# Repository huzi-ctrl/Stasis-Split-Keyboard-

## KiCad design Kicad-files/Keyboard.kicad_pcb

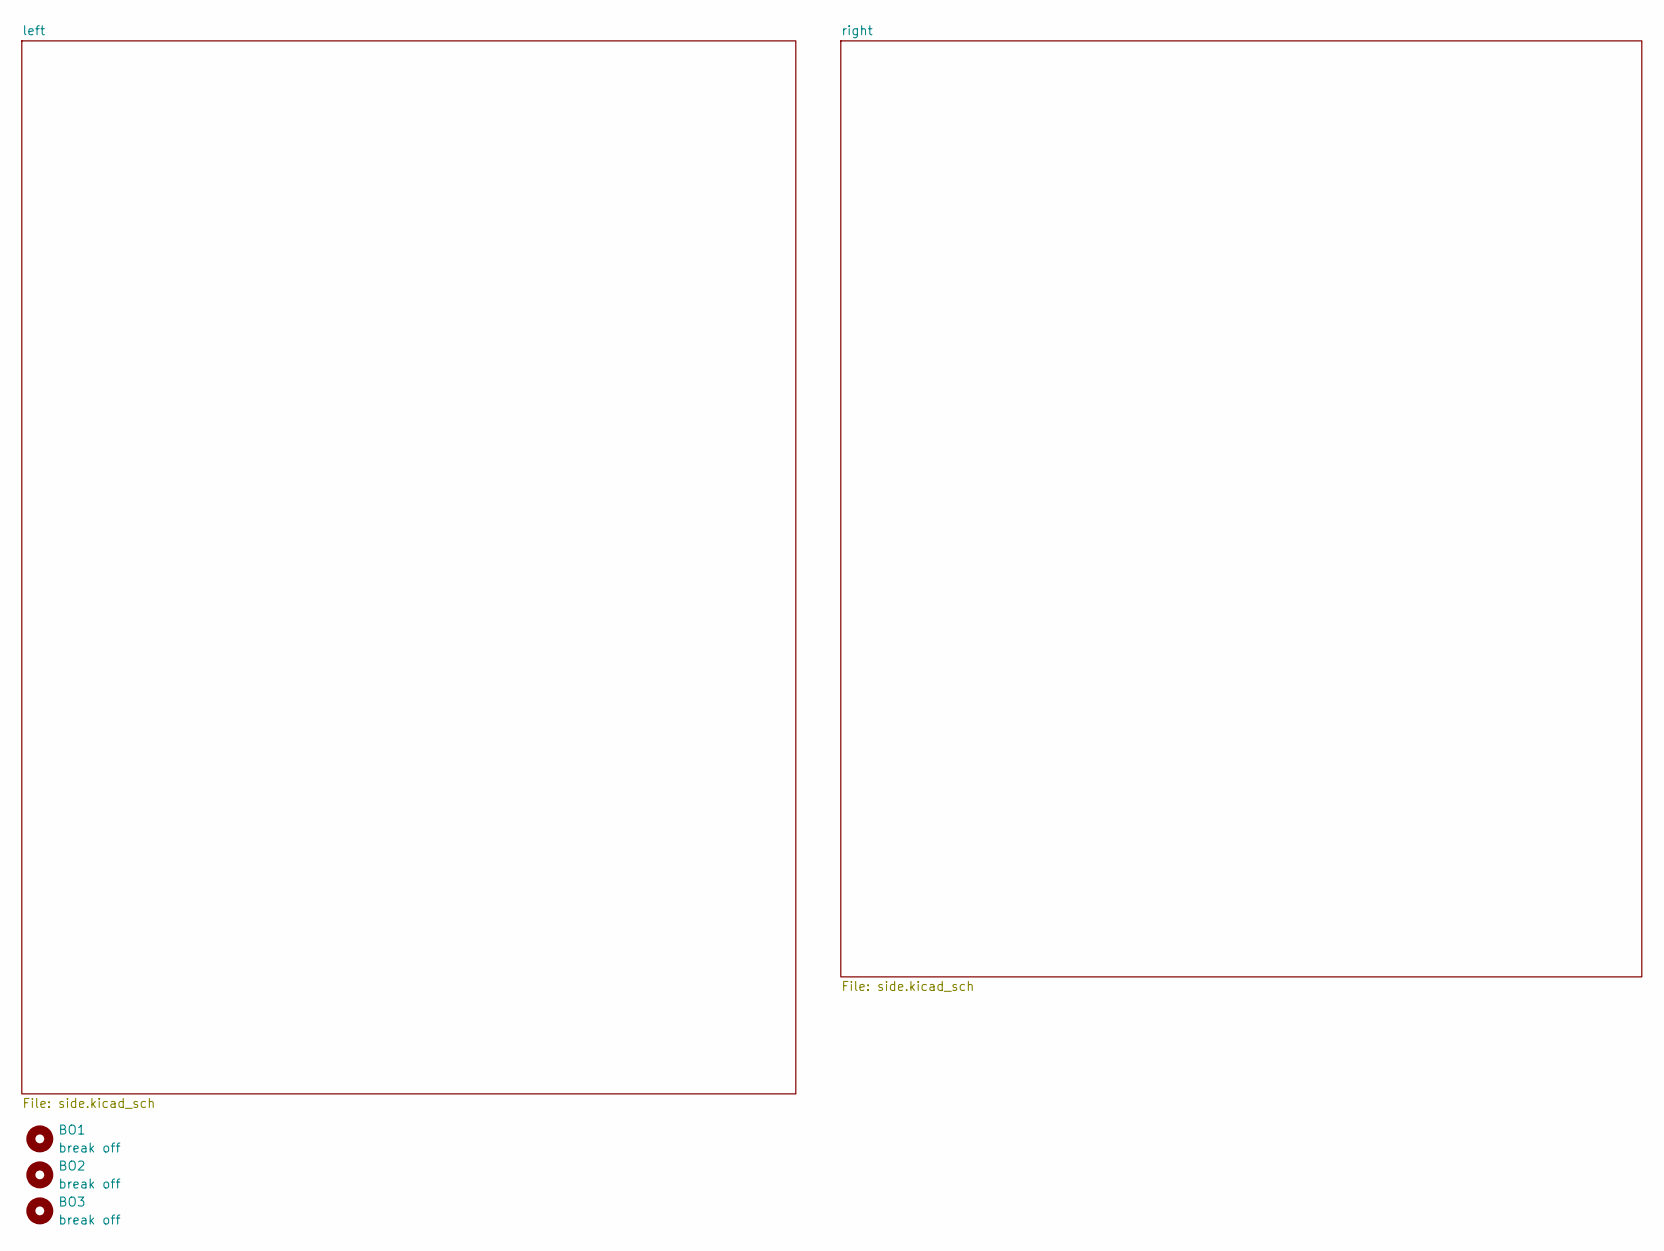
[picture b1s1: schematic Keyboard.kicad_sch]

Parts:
BO1, BO2, BO3: break off; MouseBite-Slot_2.0x4.5mm_outset_D0.5mm_P0.85mm_7h

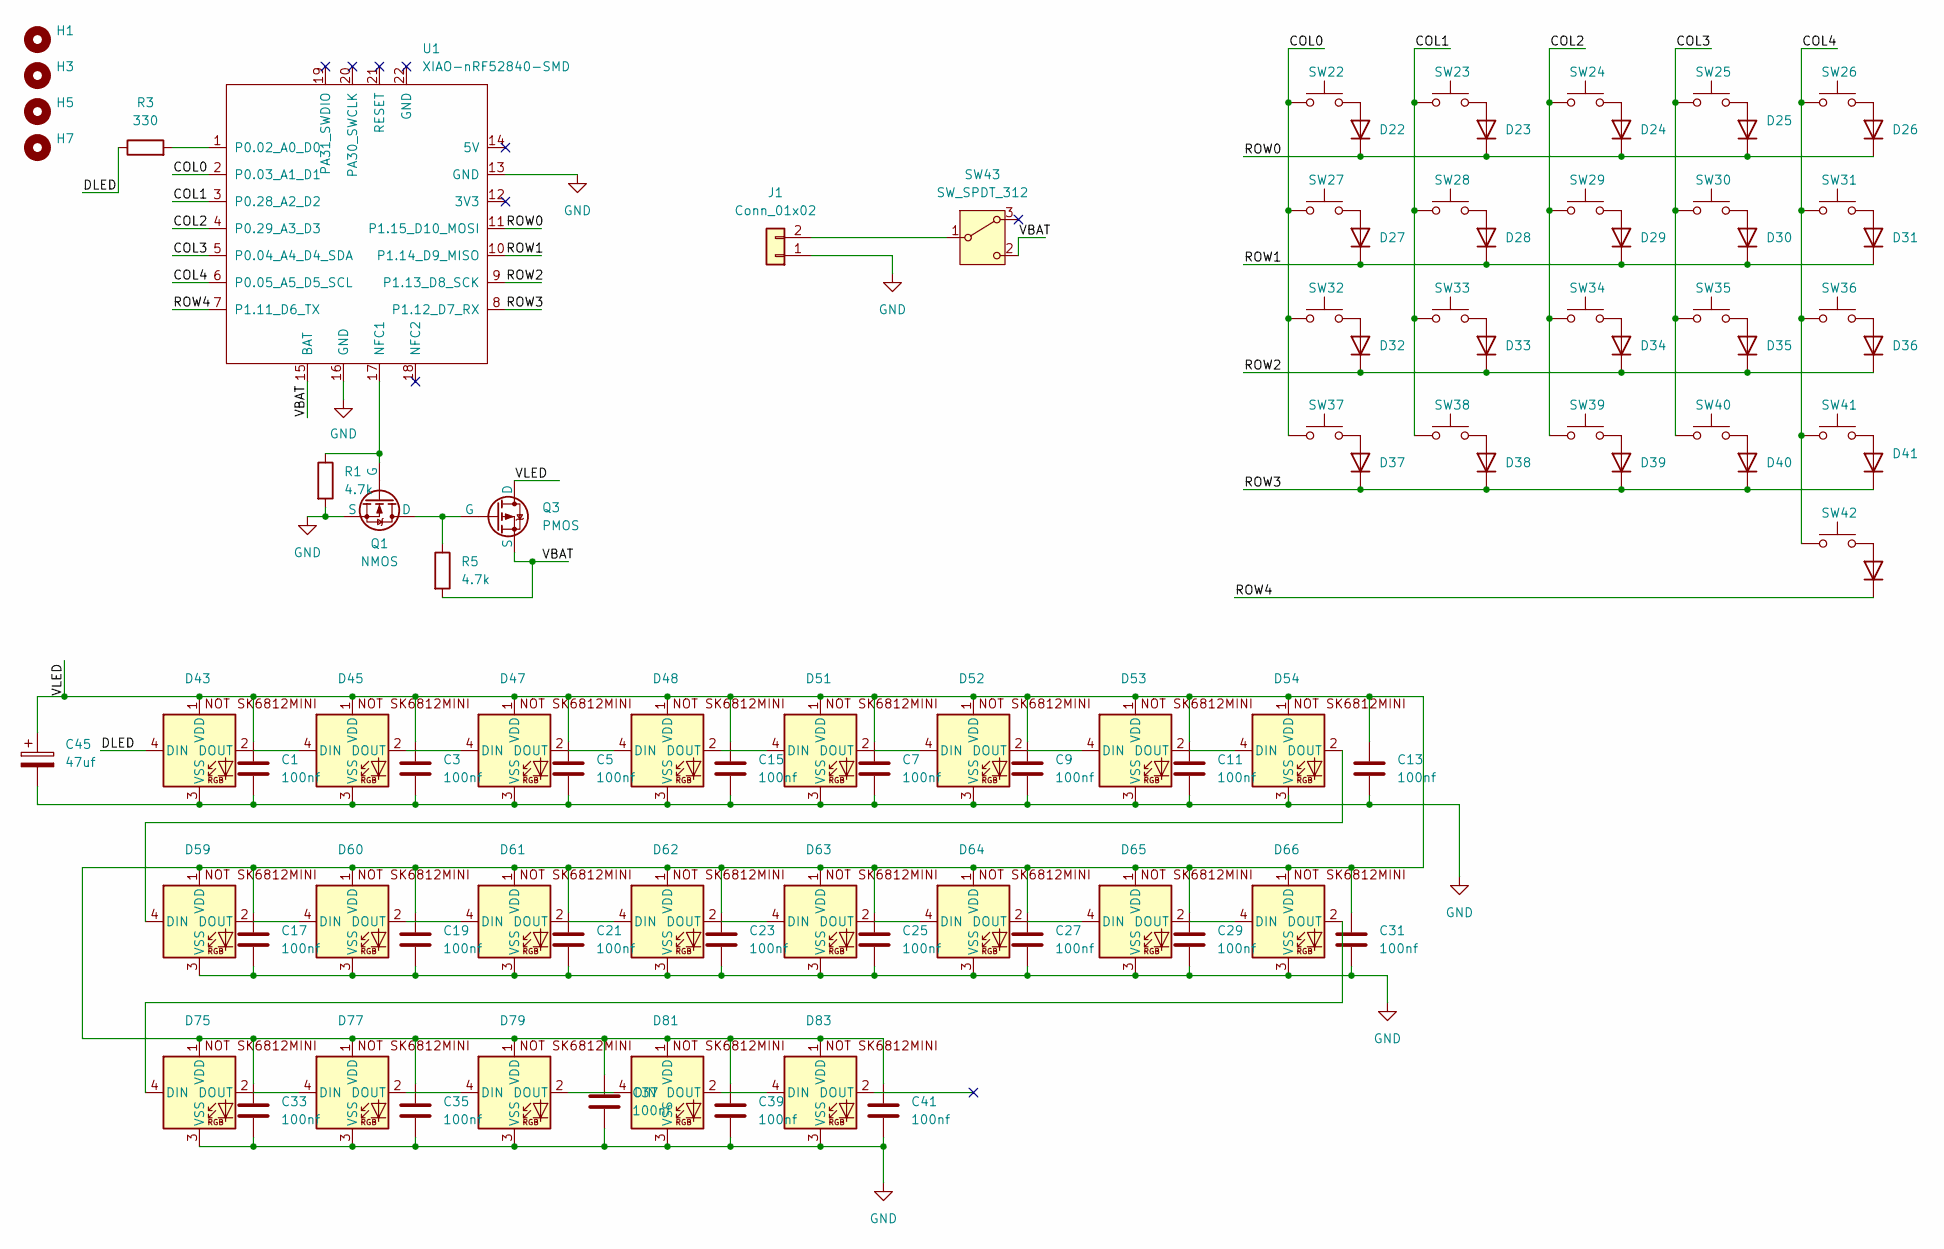
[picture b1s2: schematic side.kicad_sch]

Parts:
C1, C3, C5, C7, C9, C11, C13, C15, C17, C19, C21, C23, C25, C27, C29, C31, C33, C35, C37, C39, C41: 100nf; C_Disc_D5.0mm_W2.5mm_P5.00mm
C45: 47uf; CP_Radial_D8.0mm_P3.50mm
D22, D23, D24, D25, D26, D27, D28, D29, D30, D31, D32, D33, D34, D35, D36, D37, D38, D39, D40, D41, D42: D
D43, D45, D47, D48, D51, D52, D53, D54, D59, D60, D61, D62, D63, D64, D65, D66, D75, D77, D79, D81, D83: SK6812MINI-E; SK6812MINI-E - 3.2x2.8x1.78mm
H1, H3, H5, H7: MountingHole; MountingHole_2.2mm_M2
J1: Conn_01x02; JST_PH_S2B-PH-K_1x02_P2.00mm_Horizontal
Q1: NMOS; TO-92-2_Wide
Q3: PMOS; TO-220-3_Vertical
R1, R5: 4.7k; R_Axial_DIN0207_L6.3mm_D2.5mm_P10.16mm_Horizontal
R3: 330; R_Axial_DIN0207_L6.3mm_D2.5mm_P10.16mm_Horizontal
SW22, SW23, SW24, SW25, SW26, SW27, SW28, SW29, SW30, SW31, SW32, SW33, SW34, SW35, SW36, SW37, SW38, SW39, SW40, SW41, SW42: SW_Push
SW43: SW_SPDT_312; PinHeader_1x03_P2.54mm_Vertical
U1: XIAO-nRF52840-SMD; modified-XIAO-nRF52840-SMD

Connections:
/left/COL0: SW22.1, SW27.1, SW32.1, SW37.1, U1.2 (P0.03_A1_D1)
/left/COL1: SW23.1, SW28.1, SW33.1, SW38.1, U1.3 (P0.28_A2_D2)
/left/COL2: SW24.1, SW29.1, SW34.1, SW39.1, U1.4 (P0.29_A3_D3)
/left/COL3: SW25.1, SW30.1, SW35.1, SW40.1, U1.5 (P0.04_A4_D4_SDA)
/left/COL4: SW26.1, SW31.1, SW36.1, SW41.1, SW42.1, U1.6 (P0.05_A5_D5_SCL)
/left/DLED: D43.4 (DIN), R3.1
/left/ROW0: D22.1 (K), D23.1 (K), D24.1 (K), D25.1 (K), D26.1 (K), U1.11 (P1.15_D10_MOSI)
/left/ROW1: D27.1 (K), D28.1 (K), D29.1 (K), D30.1 (K), D31.1 (K), U1.10 (P1.14_D9_MISO)
/left/ROW2: D32.1 (K), D33.1 (K), D34.1 (K), D35.1 (K), D36.1 (K), U1.9 (P1.13_D8_SCK)
/left/ROW3: D37.1 (K), D38.1 (K), D39.1 (K), D40.1 (K), D41.1 (K), U1.8 (P1.12_D7_RX)
/left/ROW4: D42.1 (K), U1.7 (P1.11_D6_TX)
/left/VBAT: Q3.3 (S), R5.2, SW43.2 (C), U1.15 (BAT)
/left/VLED: C1.1, C3.1, C5.1, C7.1, C9.1, C11.1, C13.1, C15.1, C17.1, C19.1, C21.1, C23.1, C25.1, C27.1, C29.1, C31.1, C33.1, C35.1, C37.1, C39.1, C41.1, C45.1, D43.1 (VDD), D45.1 (VDD), D47.1 (VDD), D48.1 (VDD), D51.1 (VDD), D52.1 (VDD), D53.1 (VDD), D54.1 (VDD), D59.1 (VDD), D60.1 (VDD), D61.1 (VDD), D62.1 (VDD), D63.1 (VDD), D64.1 (VDD), D65.1 (VDD), D66.1 (VDD), D75.1 (VDD), D77.1 (VDD), D79.1 (VDD), D81.1 (VDD), D83.1 (VDD), Q3.1 (D)
GND: C1.2, C3.2, C5.2, C7.2, C9.2, C11.2, C13.2, C15.2, C17.2, C19.2, C21.2, C23.2, C25.2, C27.2, C29.2, C31.2, C33.2, C35.2, C37.2, C39.2, C41.2, C45.2, D43.3 (VSS), D45.3 (VSS), D47.3 (VSS), D48.3 (VSS), D51.3 (VSS), D52.3 (VSS), D53.3 (VSS), D54.3 (VSS), D59.3 (VSS), D60.3 (VSS), D61.3 (VSS), D62.3 (VSS), D63.3 (VSS), D64.3 (VSS), D65.3 (VSS), D66.3 (VSS), D75.3 (VSS), D77.3 (VSS), D79.3 (VSS), D81.3 (VSS), D83.3 (VSS), J1.1, Q1.3 (S), R1.2, U1.13 (GND), U1.16 (GND); also elsewhere on the board
unnamed: D22.2 (A), SW22.2
unnamed: D23.2 (A), SW23.2
unnamed: D24.2 (A), SW24.2
unnamed: D25.2 (A), SW25.2
unnamed: D26.2 (A), SW26.2
unnamed: D27.2 (A), SW27.2
unnamed: D28.2 (A), SW28.2
unnamed: D29.2 (A), SW29.2
unnamed: D30.2 (A), SW30.2
unnamed: D31.2 (A), SW31.2
unnamed: D32.2 (A), SW32.2
unnamed: D33.2 (A), SW33.2
unnamed: D34.2 (A), SW34.2
unnamed: D35.2 (A), SW35.2
unnamed: D36.2 (A), SW36.2
unnamed: D37.2 (A), SW37.2
unnamed: D38.2 (A), SW38.2
unnamed: D39.2 (A), SW39.2
unnamed: D40.2 (A), SW40.2
unnamed: D41.2 (A), SW41.2
unnamed: D42.2 (A), SW42.2
unnamed: D43.2 (DOUT), D45.4 (DIN)
unnamed: D45.2 (DOUT), D47.4 (DIN)
unnamed: D47.2 (DOUT), D48.4 (DIN)
unnamed: D48.2 (DOUT), D51.4 (DIN)
unnamed: D51.2 (DOUT), D52.4 (DIN)
unnamed: D52.2 (DOUT), D53.4 (DIN)
unnamed: D53.2 (DOUT), D54.4 (DIN)
unnamed: D54.2 (DOUT), D59.4 (DIN)
unnamed: D59.2 (DOUT), D60.4 (DIN)
unnamed: D60.2 (DOUT), D61.4 (DIN)
unnamed: D61.2 (DOUT), D62.4 (DIN)
unnamed: D62.2 (DOUT), D63.4 (DIN)
unnamed: D63.2 (DOUT), D64.4 (DIN)
unnamed: D64.2 (DOUT), D65.4 (DIN)
unnamed: D65.2 (DOUT), D66.4 (DIN)
unnamed: D66.2 (DOUT), D75.4 (DIN)
unnamed: D75.2 (DOUT), D77.4 (DIN)
unnamed: D77.2 (DOUT), D79.4 (DIN)
unnamed: D79.2 (DOUT), D81.4 (DIN)
unnamed: D81.2 (DOUT), D83.4 (DIN)
unnamed: J1.2, SW43.1 (B)
unnamed: Q1.1 (D), Q3.2 (G), R5.1
unnamed: Q1.2 (G), R1.1, U1.17 (NFC1)
unnamed: R3.2, U1.1 (P0.02_A0_D0)

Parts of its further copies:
C2, C4, C6, C8, C10, C12, C14, C16, C18, C20, C22, C24, C26, C28, C30, C32, C34, C36, C38, C40, C42: 100nf; C_Disc_D5.0mm_W2.5mm_P5.00mm
C46: 47uf; CP_Radial_D8.0mm_P3.50mm
D1, D2, D3, D4, D5, D6, D7, D8, D9, D10, D11, D12, D13, D14, D15, D16, D17, D18, D19, D20, D21: D
D44, D46, D49, D50, D55, D56, D57, D58, D67, D68, D69, D70, D71, D72, D73, D74, D91, D93, D95, D97, D99: SK6812MINI-E; SK6812MINI-E - 3.2x2.8x1.78mm
H2, H4, H6, H8: MountingHole; MountingHole_2.2mm_M2
J2: Conn_01x02; JST_PH_S2B-PH-K_1x02_P2.00mm_Horizontal
Q2: NMOS; TO-92-2_Wide
Q4: PMOS; TO-220-3_Vertical
R2, R6: 4.7k; R_Axial_DIN0207_L6.3mm_D2.5mm_P10.16mm_Horizontal
R4: 330; R_Axial_DIN0207_L6.3mm_D2.5mm_P10.16mm_Horizontal
SW1, SW2, SW3, SW4, SW5, SW6, SW7, SW8, SW9, SW10, SW11, SW12, SW13, SW14, SW15, SW16, SW17, SW18, SW19, SW20, SW21: SW_Push
SW44: SW_SPDT_312; PinHeader_1x03_P2.54mm_Vertical
U2: XIAO-nRF52840-SMD; modified-XIAO-nRF52840-SMD

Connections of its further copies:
/right/COL0: SW1.1, SW6.1, SW11.1, SW16.1, U2.2 (P0.03_A1_D1)
/right/COL1: SW2.1, SW7.1, SW12.1, SW17.1, U2.3 (P0.28_A2_D2)
/right/COL2: SW3.1, SW8.1, SW13.1, SW18.1, U2.4 (P0.29_A3_D3)
/right/COL3: SW4.1, SW9.1, SW14.1, SW19.1, U2.5 (P0.04_A4_D4_SDA)
/right/COL4: SW5.1, SW10.1, SW15.1, SW20.1, SW21.1, U2.6 (P0.05_A5_D5_SCL)
/right/DLED: D44.4 (DIN), R4.1
/right/ROW0: D1.1 (K), D2.1 (K), D3.1 (K), D4.1 (K), D5.1 (K), U2.11 (P1.15_D10_MOSI)
/right/ROW1: D6.1 (K), D7.1 (K), D8.1 (K), D9.1 (K), D10.1 (K), U2.10 (P1.14_D9_MISO)
/right/ROW2: D11.1 (K), D12.1 (K), D13.1 (K), D14.1 (K), D15.1 (K), U2.9 (P1.13_D8_SCK)
/right/ROW3: D16.1 (K), D17.1 (K), D18.1 (K), D19.1 (K), D20.1 (K), U2.8 (P1.12_D7_RX)
/right/ROW4: D21.1 (K), U2.7 (P1.11_D6_TX)
/right/VBAT: Q4.3 (S), R6.2, SW44.2 (C), U2.15 (BAT)
/right/VLED: C2.1, C4.1, C6.1, C8.1, C10.1, C12.1, C14.1, C16.1, C18.1, C20.1, C22.1, C24.1, C26.1, C28.1, C30.1, C32.1, C34.1, C36.1, C38.1, C40.1, C42.1, C46.1, D44.1 (VDD), D46.1 (VDD), D49.1 (VDD), D50.1 (VDD), D55.1 (VDD), D56.1 (VDD), D57.1 (VDD), D58.1 (VDD), D67.1 (VDD), D68.1 (VDD), D69.1 (VDD), D70.1 (VDD), D71.1 (VDD), D72.1 (VDD), D73.1 (VDD), D74.1 (VDD), D91.1 (VDD), D93.1 (VDD), D95.1 (VDD), D97.1 (VDD), D99.1 (VDD), Q4.1 (D)
GND: C2.2, C4.2, C6.2, C8.2, C10.2, C12.2, C14.2, C16.2, C18.2, C20.2, C22.2, C24.2, C26.2, C28.2, C30.2, C32.2, C34.2, C36.2, C38.2, C40.2, C42.2, C46.2, D44.3 (VSS), D46.3 (VSS), D49.3 (VSS), D50.3 (VSS), D55.3 (VSS), D56.3 (VSS), D57.3 (VSS), D58.3 (VSS), D67.3 (VSS), D68.3 (VSS), D69.3 (VSS), D70.3 (VSS), D71.3 (VSS), D72.3 (VSS), D73.3 (VSS), D74.3 (VSS), D91.3 (VSS), D93.3 (VSS), D95.3 (VSS), D97.3 (VSS), D99.3 (VSS), J2.1, R2.2, U2.13 (GND), U2.16 (GND); also elsewhere on the board
unnamed: D1.2 (A), SW1.2
unnamed: D2.2 (A), SW2.2
unnamed: D3.2 (A), SW3.2
unnamed: D4.2 (A), SW4.2
unnamed: D5.2 (A), SW5.2
unnamed: D6.2 (A), SW6.2
unnamed: D7.2 (A), SW7.2
unnamed: D8.2 (A), SW8.2
unnamed: D9.2 (A), SW9.2
unnamed: D10.2 (A), SW10.2
unnamed: D11.2 (A), SW11.2
unnamed: D12.2 (A), SW12.2
unnamed: D13.2 (A), SW13.2
unnamed: D14.2 (A), SW14.2
unnamed: D15.2 (A), SW15.2
unnamed: D16.2 (A), SW16.2
unnamed: D17.2 (A), SW17.2
unnamed: D18.2 (A), SW18.2
unnamed: D19.2 (A), SW19.2
unnamed: D20.2 (A), SW20.2
unnamed: D21.2 (A), SW21.2
unnamed: D44.2 (DOUT), D46.4 (DIN)
unnamed: D46.2 (DOUT), D49.4 (DIN)
unnamed: D49.2 (DOUT), D50.4 (DIN)
unnamed: D50.2 (DOUT), D55.4 (DIN)
unnamed: D55.2 (DOUT), D56.4 (DIN)
unnamed: D56.2 (DOUT), D57.4 (DIN)
unnamed: D57.2 (DOUT), D58.4 (DIN)
unnamed: D58.2 (DOUT), D67.4 (DIN)
unnamed: D67.2 (DOUT), D68.4 (DIN)
unnamed: D68.2 (DOUT), D69.4 (DIN)
unnamed: D69.2 (DOUT), D70.4 (DIN)
unnamed: D70.2 (DOUT), D71.4 (DIN)
unnamed: D71.2 (DOUT), D72.4 (DIN)
unnamed: D72.2 (DOUT), D73.4 (DIN)
unnamed: D73.2 (DOUT), D74.4 (DIN)
unnamed: D74.2 (DOUT), D91.4 (DIN)
unnamed: D91.2 (DOUT), D93.4 (DIN)
unnamed: D93.2 (DOUT), D95.4 (DIN)
unnamed: D95.2 (DOUT), D97.4 (DIN)
unnamed: D97.2 (DOUT), D99.4 (DIN)
unnamed: J2.2, SW44.1 (B)
unnamed: Q2.1 (D), Q4.2 (G), R6.1
unnamed: Q2.2 (G), R2.1, U2.17 (NFC1)
unnamed: R4.2, U2.1 (P0.02_A0_D0)

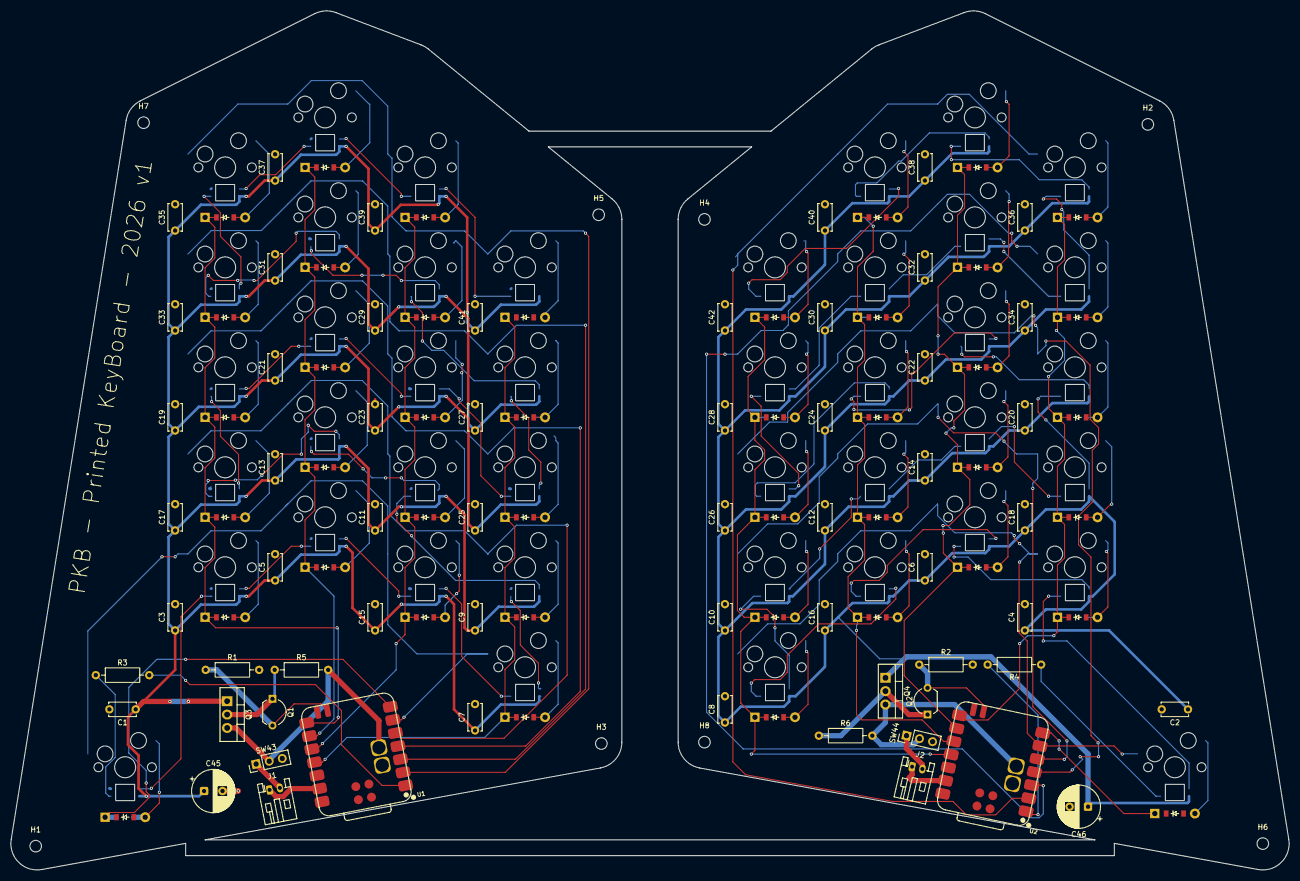
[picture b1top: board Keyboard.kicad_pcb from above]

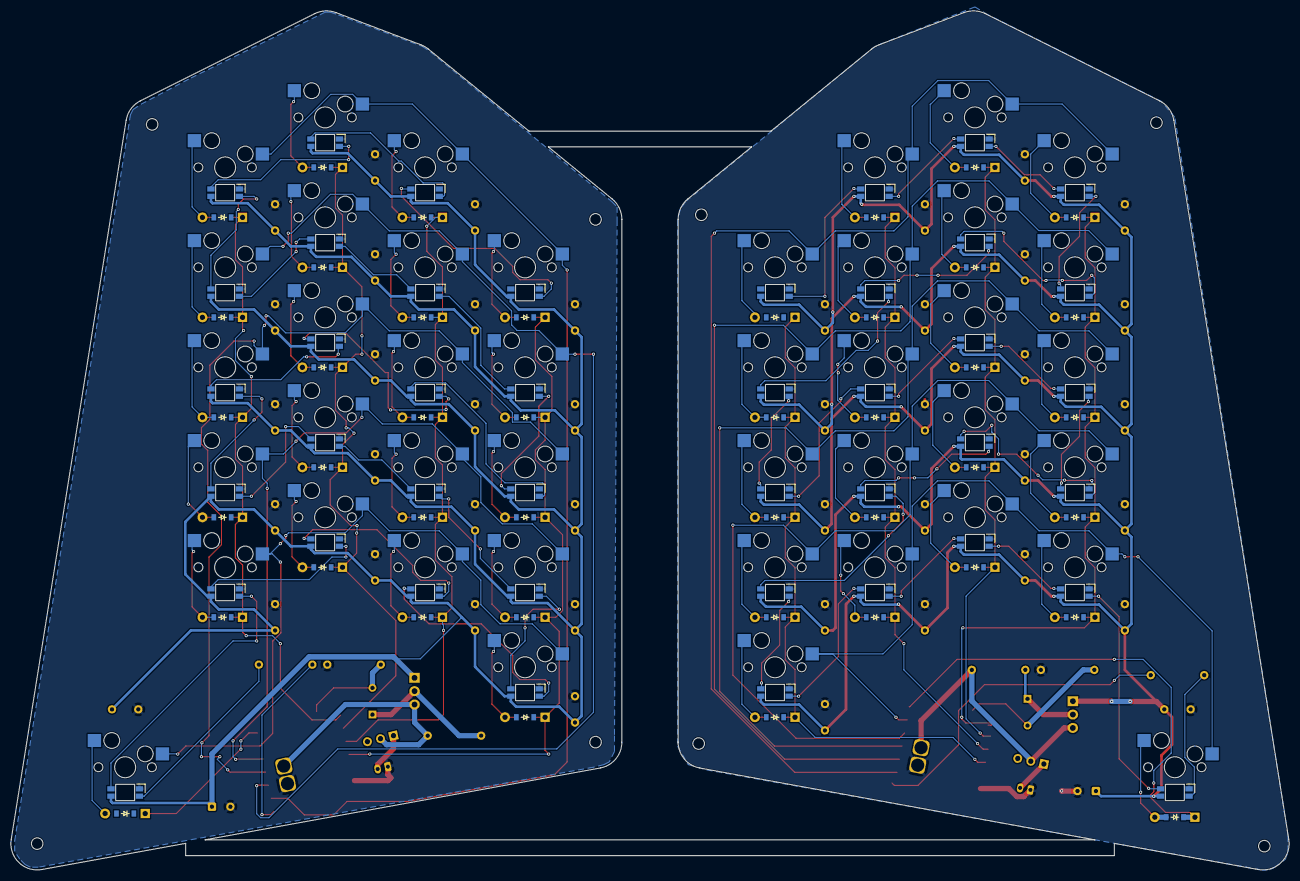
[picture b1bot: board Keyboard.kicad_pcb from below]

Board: 2 copper layers, 242.9 x 163.3 mm, 194 parts (42 on the bottom side), 117 nets.

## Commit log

2026-05-02 Add files via upload
    Added Kicad Project files
2026-05-02 Create
2026-05-02 Adding KiCad files
2026-05-02 Moved files
2026-05-02 Uploaded Production outputs
    Uploaded Production outputs
2026-05-08 added firmware
